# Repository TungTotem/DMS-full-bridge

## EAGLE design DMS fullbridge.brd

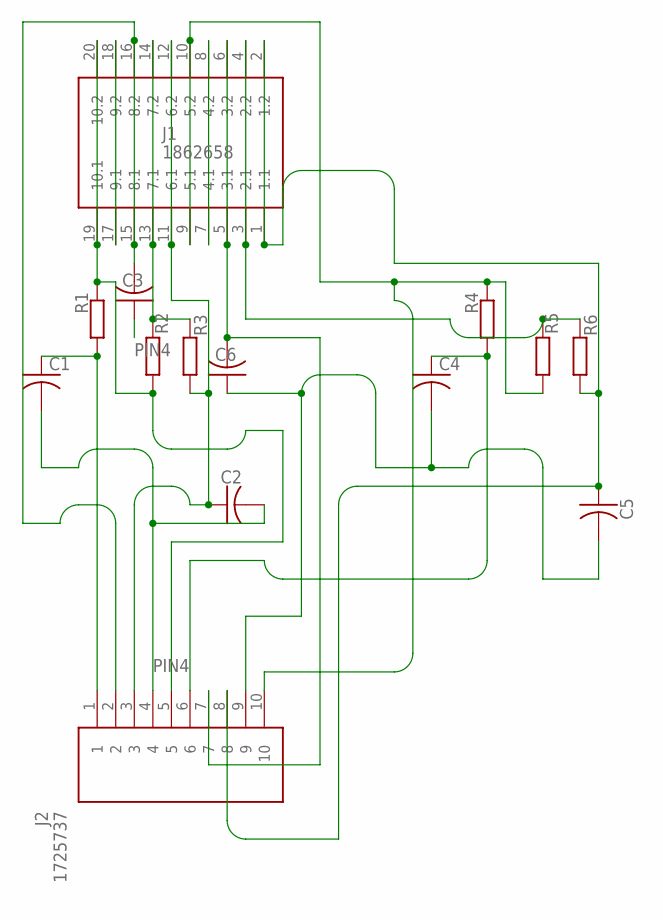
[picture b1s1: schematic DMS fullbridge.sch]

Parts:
C1, C2, C3, C4, C5, C6: C-US050-030X075; C050-030X075
J1: 1862658
J2: 1725737
R1, R2, R3, R4, R5, R6: R-EU_0204/7; 0204/7

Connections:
3: C2.1, J1.11 (6.1), J1.12 (6.2), J2.3, R3.1
9: C4.2, C5.2, C6.1, J2.9
AIN1.1: C6.2, J1.5 (3.1), J1.6 (3.2), J2.7
AIN1.3: C3.2, J1.15 (8.1), J1.16 (8.2), J2.2
unnamed: J1.3 (2.1), J1.4 (2.2), R5.2, R6.2
unnamed: J1.13 (7.1), J1.14 (7.2), R2.2, R3.2
unnamed: J1.17 (9.1), J1.18 (9.2)
unnamed: J1.7 (4.1), J1.8 (4.2)
ONE: C1.1, C4.1, J2.1, J2.6, R1.1, R4.1
PIN4: C1.2, C2.2, C3.1, J2.4
PIN8: C5.1, J1.1 (1.1), J1.2 (1.2), J2.8, R6.1
UF.1: J1.19 (10.1), J1.20 (10.2), J2.5, R1.2, R2.1
UF.2: J1.9 (5.1), J1.10 (5.2), J2.10, R4.2, R5.1

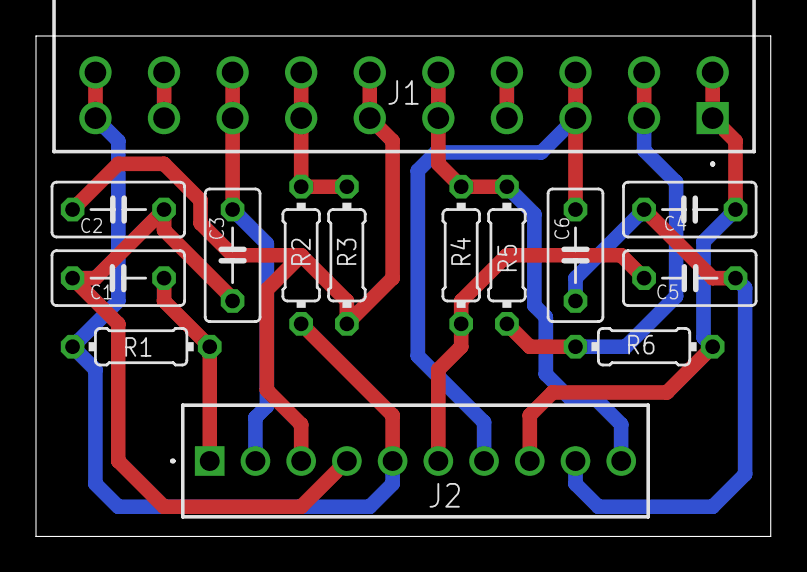
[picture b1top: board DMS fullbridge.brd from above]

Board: 2 copper layers, 40.8 x 27.8 mm, 14 parts (0 on the bottom side), 13 nets.
